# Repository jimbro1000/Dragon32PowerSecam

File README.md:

# SECAM Dragon 32 Power Board

This project is a historic record of the Dragon 32 SECAM power board.
Part Number 41504. This is not intended for fabrication but should be
dimensionally correct.

The board is unique in that it contains a full YPrPb conversion to
RGB - something very lacking from the original design

## Compatibility

This board can only be used with a SECAM version of the main CPU
board, see https://github.com/jimbro1000/Dragon32Issue2aSecam

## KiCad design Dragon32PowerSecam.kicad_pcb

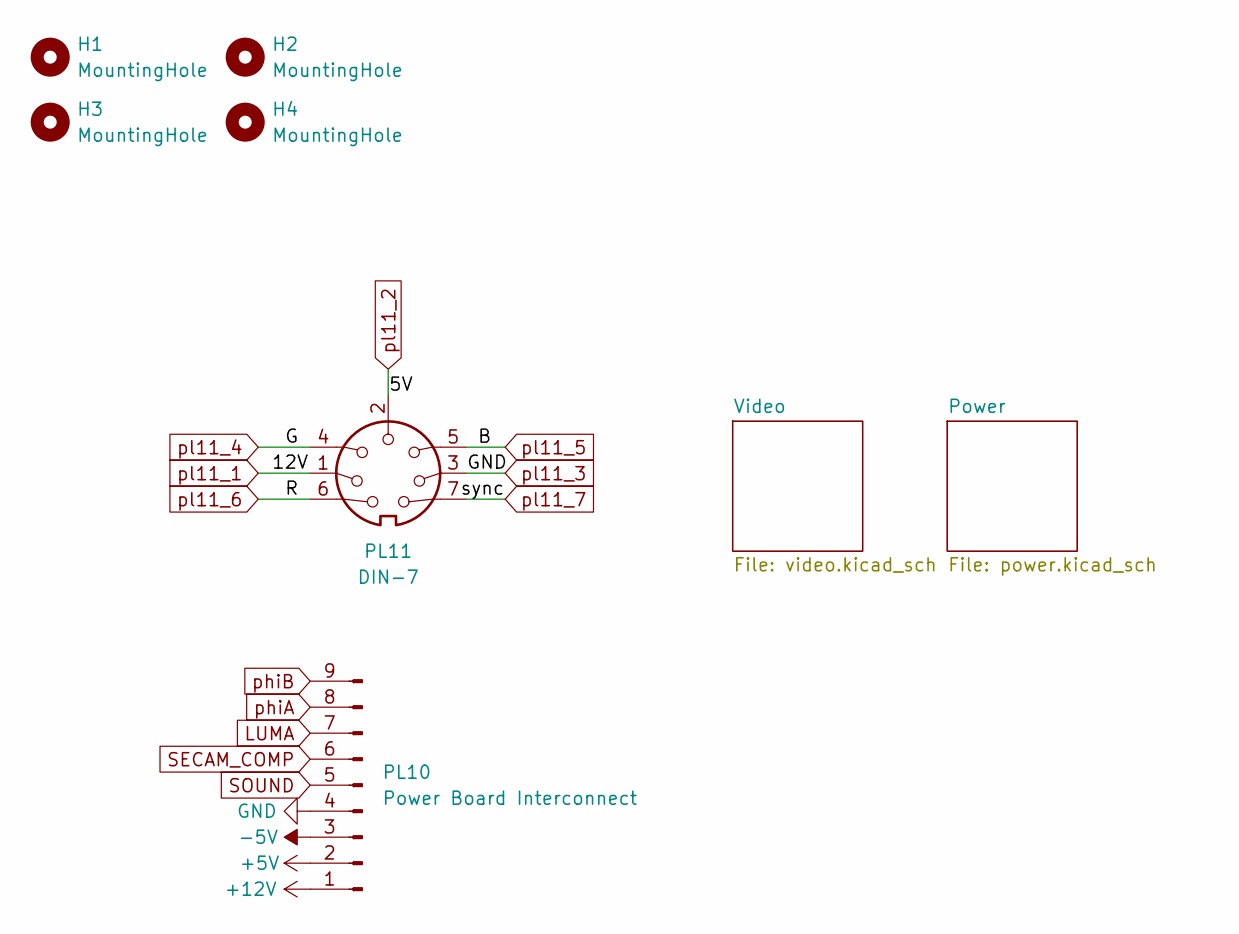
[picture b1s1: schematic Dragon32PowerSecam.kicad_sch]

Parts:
H1, H2, H3, H4: MountingHole; MountingHole_3.2mm_M3
PL10: Power Board Interconnect; Molex_KK-396_A-41791-0009_1x09_P3.96mm_Vertical; DigiKey 2057-LHD-09-TS-ND
PL11: DIN-7; CUI_SDS-70J; DigiKey CP-2370-ND

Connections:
+5V: PL10.2; also elsewhere on the board
+12V: PL10.1; also elsewhere on the board
-5V: PL10.3; also elsewhere on the board
LUMA: PL10.7; also elsewhere on the board
SECAM_COMP: PL10.6; also elsewhere on the board
SOUND: PL10.5; also elsewhere on the board
phiA: PL10.8; also elsewhere on the board
phiB: PL10.9; also elsewhere on the board
pl11_1: PL11.1; also elsewhere on the board
pl11_2: PL11.2; also elsewhere on the board
pl11_3: PL10.4, PL11.3; also elsewhere on the board
pl11_4: PL11.4; also elsewhere on the board
pl11_5: PL11.5; also elsewhere on the board
pl11_6: PL11.6; also elsewhere on the board
pl11_7: PL11.7; also elsewhere on the board

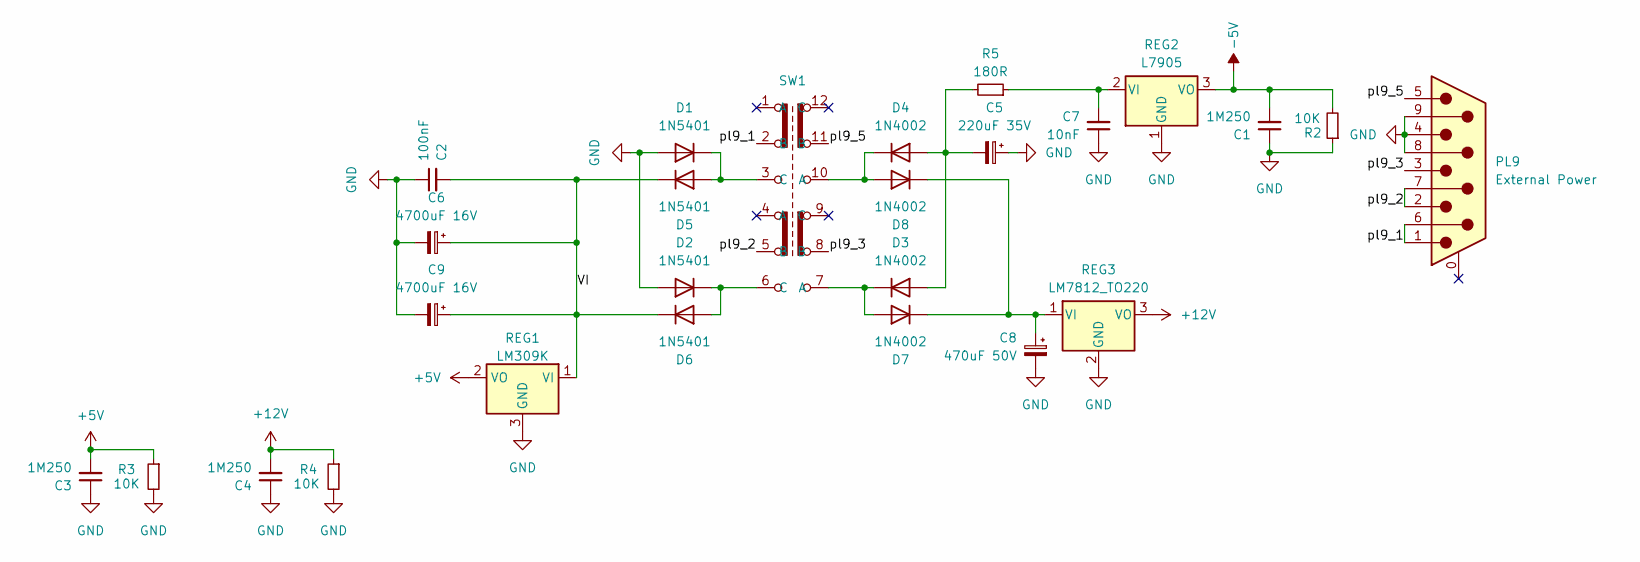
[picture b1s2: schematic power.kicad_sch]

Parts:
C1, C3, C4: 1M250; C_Rect_L16.5mm_W5.0mm_P15.00mm_MKT
C2: 100nF; C_Disc_D4.3mm_W1.9mm_P5.00mm
C5: 220uF 35V; CP_Axial_L25.0mm_D10.0mm_P30.00mm_Horizontal
C6, C9: 4700uF 16V; CP_Axial_L34.5mm_D20.0mm_P41.00mm_Horizontal
C7: 10nF; C_Disc_D4.7mm_W2.5mm_P5.00mm
C8: 470uF 50V; CP_Axial_L30.0mm_D10.0mm_P35.00mm_Horizontal
D1, D2, D5, D6: 1N5401; D_DO-201AD_P15.24mm_Horizontal
D3, D4, D7, D8: 1N4002; D_DO-41_SOD81_P10.16mm_Horizontal
PL9: External Power; DSUB-9_Male_Horizontal_P2.77x2.84mm_EdgePinOffset9.90mm_Hou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
R2, R3, R4: 10K; R_Axial_DIN0309_L9.0mm_D2.5mm_P12.70mm_Horizontal
R5: 180R; R_Axial_DIN0516_L15.5mm_D5.0mm_P20.32mm_Horizontal
REG1: LM309K; TO-3
REG2: L7905; TO-220-3_Vertical
REG3: LM7812_TO220; TO-220-3_Vertical
SW1: Switch_Push_Interlock_4P2T

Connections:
+5V: C3.2, R3.1, REG1.2 (VO); also elsewhere on the board
+12V: C4.2, R4.1, REG3.3 (VO); also elsewhere on the board
-5V: C1.2, R2.2, REG2.3 (VO); also elsewhere on the board
/Power/VI: C2.2, C6.1, C9.1, D5.1 (K), D6.1 (K), REG1.1 (VI)
/Power/pl9_1: PL9.1, PL9.6, SW1.2 (B)
/Power/pl9_2: PL9.2, PL9.7, SW1.5 (B)
/Power/pl9_3: PL9.3, SW1.8 (B)
/Power/pl9_5: PL9.5, SW1.11 (B)
unnamed: D1.1 (K), D5.2 (A), SW1.3 (C)
unnamed: D2.1 (K), D6.2 (A), SW1.6 (C)
unnamed: C5.2, D3.2 (A), D4.2 (A), R5.2
unnamed: D3.1 (K), D7.2 (A), SW1.7 (A)
unnamed: D4.1 (K), D8.2 (A), SW1.10 (A)
unnamed: C8.1, D7.1 (K), D8.1 (K), REG3.1 (VI)
unnamed: C7.2, R5.1, REG2.2 (VI)
pl11_3: C1.1, C2.1, C3.1, C4.1, C5.1, C6.2, C7.1, C8.2, C9.2, D1.2 (A), D2.2 (A), PL9.4, PL9.8, PL9.9, R2.1, R3.2, R4.2, REG1.3 (GND), REG2.1 (GND), REG3.2 (GND); also elsewhere on the board

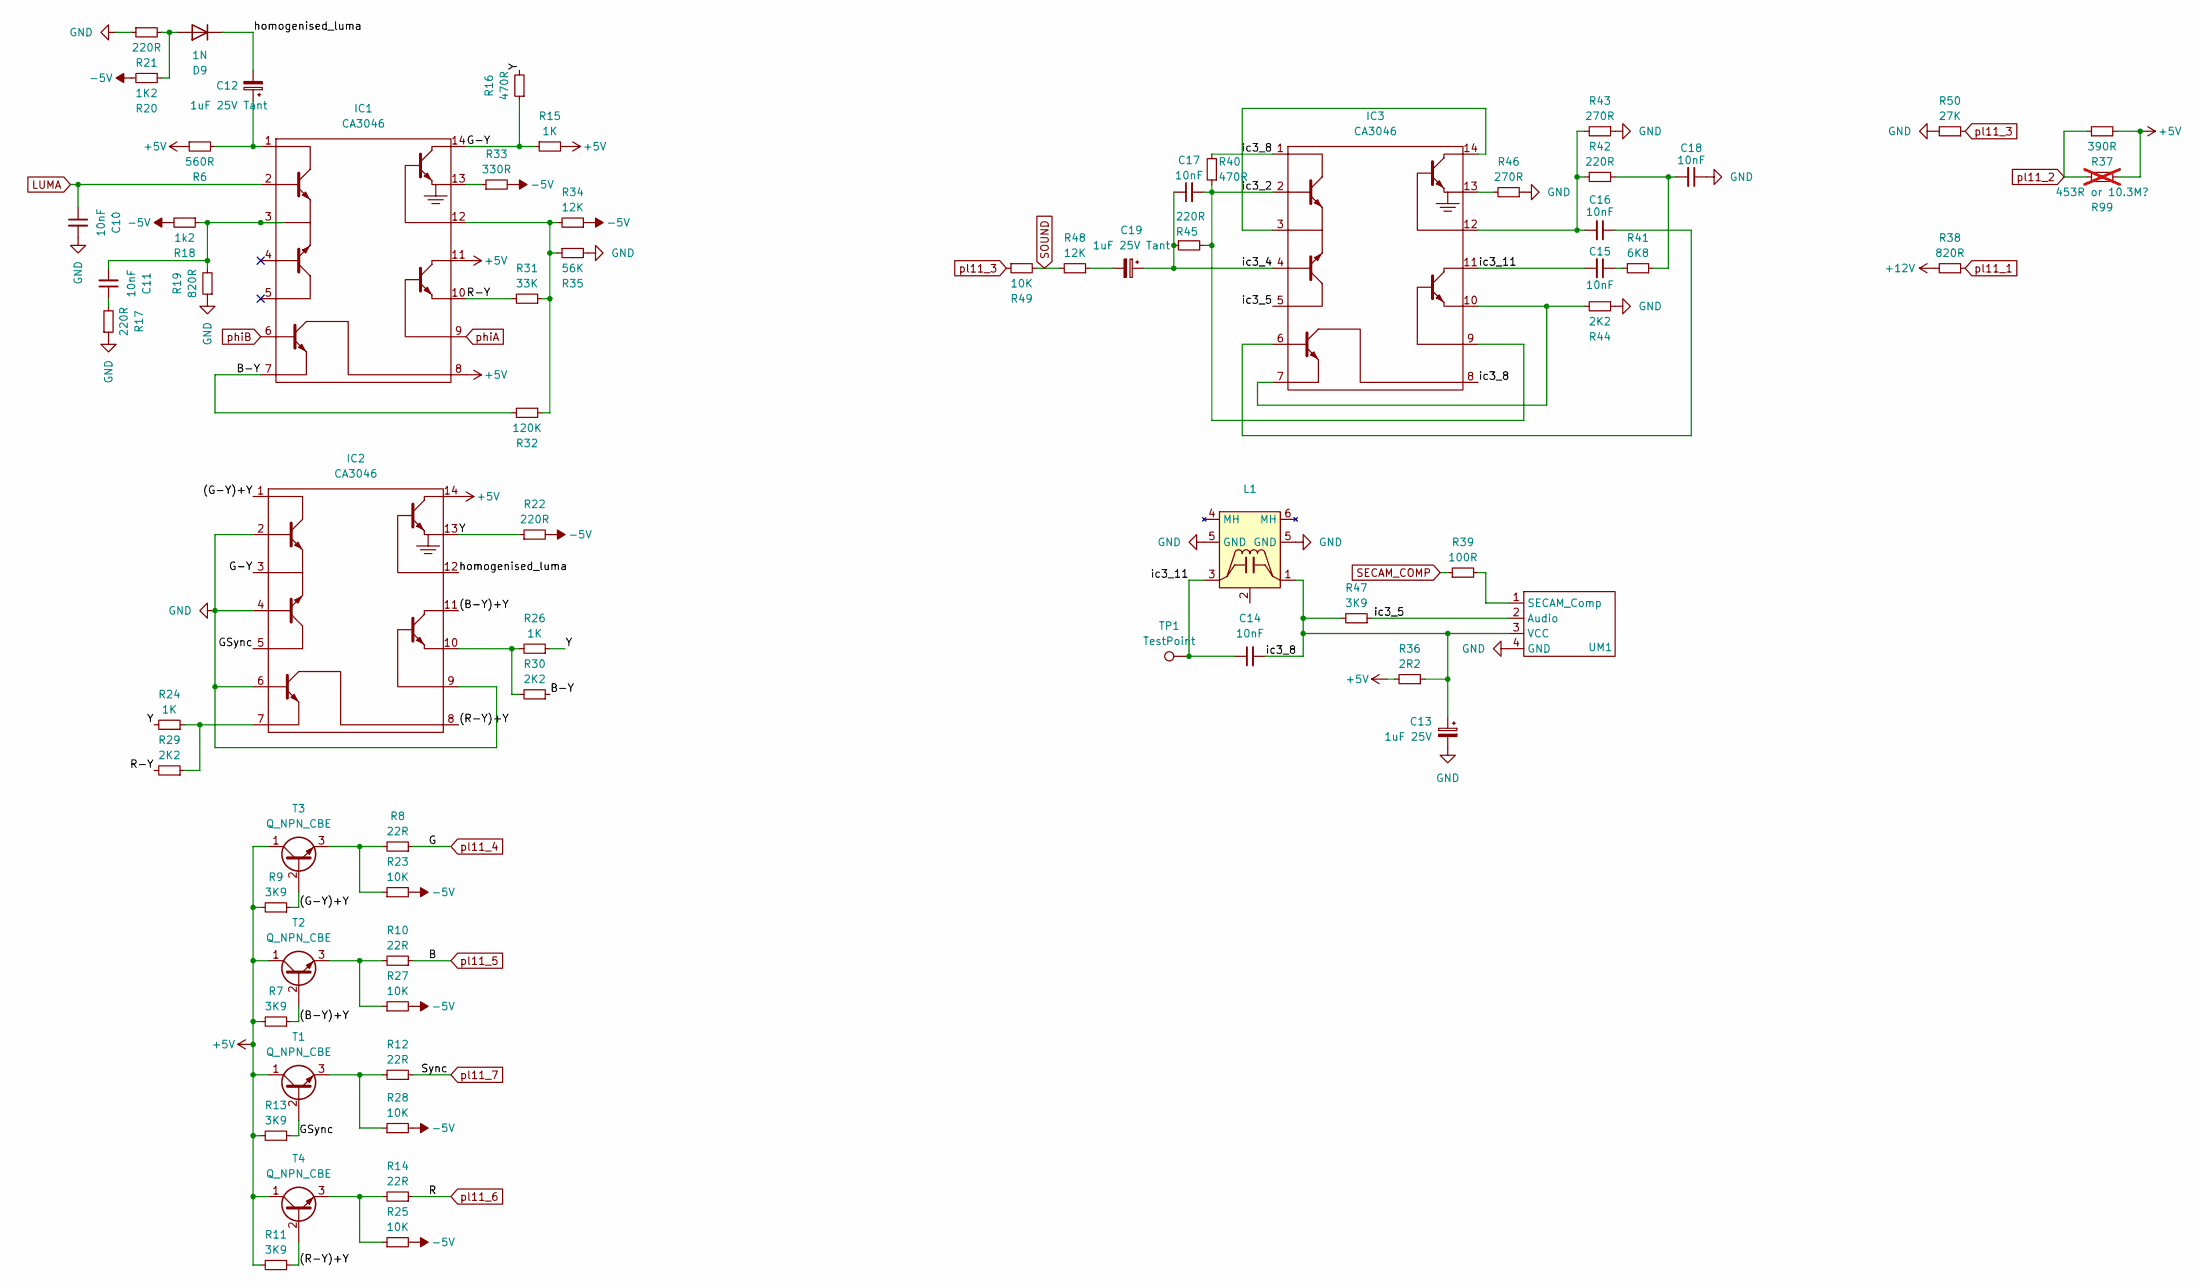
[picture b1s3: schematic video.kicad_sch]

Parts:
C10, C16: 10nF; C_Disc_D3.4mm_W2.1mm_P2.50mm
C11, C14: 10nF; C_Disc_D3.0mm_W2.0mm_P2.50mm
C12, C19: 1uF 25V Tant; CP_Radial_Tantal_D4.5mm_P5.00mm
C13: 1uF 25V; CP_Radial_Tantal_D4.5mm_P5.00mm
C15, C17, C18: 10nF; C_Disc_D4.3mm_W1.9mm_P5.00mm
D9: 1N; D_A-405_P12.70mm_Horizontal
IC1, IC2, IC3: CA3046; DIP-14_W7.62mm
L1: TOKO_RCL_10K
R6: 560R; R_Axial_DIN0309_L9.0mm_D2.5mm_P12.70mm_Horizontal
R7, R9, R11, R13, R47: 3K9; R_Axial_DIN0309_L9.0mm_D2.5mm_P12.70mm_Horizontal
R8, R10, R12, R14: 22R; R_Axial_DIN0309_L9.0mm_D2.5mm_P12.70mm_Horizontal
R15, R24, R26: 1K; R_Axial_DIN0309_L9.0mm_D2.5mm_P12.70mm_Horizontal
R16, R40: 470R; R_Axial_DIN0309_L9.0mm_D2.5mm_P12.70mm_Horizontal
R17, R21, R22, R42, R45: 220R; R_Axial_DIN0309_L9.0mm_D2.5mm_P12.70mm_Horizontal
R18: 1k2; R_Axial_DIN0207_L6.3mm_D2.5mm_P10.16mm_Horizontal
R19, R38: 820R; R_Axial_DIN0309_L9.0mm_D2.5mm_P12.70mm_Horizontal
R20: 1K2; R_Axial_DIN0207_L6.3mm_D2.5mm_P10.16mm_Horizontal
R23, R25, R27, R28, R49: 10K; R_Axial_DIN0309_L9.0mm_D2.5mm_P12.70mm_Horizontal
R29, R30, R44: 2K2; R_Axial_DIN0309_L9.0mm_D2.5mm_P12.70mm_Horizontal
R31: 33K; R_Axial_DIN0309_L9.0mm_D2.5mm_P12.70mm_Horizontal
R32: 120K; R_Axial_DIN0309_L9.0mm_D2.5mm_P12.70mm_Horizontal
R33: 330R; R_Axial_DIN0309_L9.0mm_D2.5mm_P12.70mm_Horizontal
R34, R48: 12K; R_Axial_DIN0309_L9.0mm_D2.5mm_P12.70mm_Horizontal
R35: 56K; R_Axial_DIN0309_L9.0mm_D2.5mm_P12.70mm_Horizontal
R36: 2R2; R_Axial_DIN0309_L9.0mm_D2.5mm_P12.70mm_Horizontal
R37: 390R; R_Axial_DIN0309_L9.0mm_D2.5mm_P12.70mm_Horizontal
R39: 100R; R_Axial_DIN0309_L9.0mm_D2.5mm_P12.70mm_Horizontal
R41: 6K8; R_Axial_DIN0309_L9.0mm_D2.5mm_P12.70mm_Horizontal
R43, R46: 270R; R_Axial_DIN0309_L9.0mm_D2.5mm_P12.70mm_Horizontal
R50: 27K; R_Axial_DIN0309_L9.0mm_D2.5mm_P12.70mm_Horizontal
R99: 453R or 10.3M?; R_Axial_DIN0309_L9.0mm_D2.5mm_P12.70mm_Horizontal; not fitted
T1, T2, T3, T4: Q_NPN_CBE; TO-92_Wide
TP1: TestPoint; TestPoint_THTPad_D1.0mm_Drill0.5mm
UM1: RF_Modulator_Astec_UM1601

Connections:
+5V: IC1.8, IC1.11, IC2.14, R6.1, R7.2, R9.2, R11.2, R13.2, R15.2, R36.2, R37.2, R99.2, T1.1 (C), T2.1 (C), T3.1 (C), T4.1 (C); also elsewhere on the board
+12V: R38.2; also elsewhere on the board
-5V: R18.2, R20.2, R22.2, R23.2, R25.2, R27.2, R28.2, R33.2, R34.1; also elsewhere on the board
/Video/(B-Y)+Y: IC2.11, R7.1, T2.2 (B)
/Video/(G-Y)+Y: IC2.1, R9.1, T3.2 (B)
/Video/(R-Y)+Y: IC2.8, R11.1, T4.2 (B)
/Video/B-Y: IC1.7, R30.1, R32.2
/Video/G-Y: IC1.14, IC2.3, R15.1, R16.1
/Video/GSync: IC2.5, R13.1, T1.2 (B)
/Video/R-Y: IC1.10, R29.2, R31.2
/Video/Y: IC2.13, R16.2, R22.1, R24.2, R26.1
/Video/homogenised_luma: C12.2, D9.1 (K), IC2.12
/Video/ic3_2: C17.2, IC3.2, IC3.9, R40.1, R45.2
/Video/ic3_4: C17.1, C19.1, IC3.4, R45.1
/Video/ic3_5: IC3.5, R47.1, UM1.2 (Audio)
/Video/ic3_8: C13.1, C14.2, IC3.1, IC3.8, L1.1, R36.1, R40.2, R47.2, UM1.3 (VCC)
/Video/ic3_11: C14.1, C15.2, IC3.11, L1.3, TP1.1
LUMA: C10.1, IC1.2; also elsewhere on the board
unnamed: C11.1, R17.2
unnamed: C11.2, IC1.3, R18.1, R19.2
unnamed: C12.1, IC1.1, R6.2
unnamed: C15.1, R41.2
unnamed: C16.1, IC3.6
unnamed: C16.2, IC3.12, R42.2, R43.2
unnamed: C18.2, R41.1, R42.1
unnamed: C19.2, R48.1
unnamed: D9.2 (A), R20.1, R21.2
unnamed: IC1.12, R31.1, R32.1, R34.2, R35.1
unnamed: IC1.13, R33.1
unnamed: IC2.7, R24.1, R29.1
unnamed: IC2.10, R26.2, R30.2
unnamed: IC3.7, IC3.10, R44.2
unnamed: IC3.13, R46.2
unnamed: IC3.3, IC3.14
unnamed: R12.2, R28.1, T1.3 (E)
unnamed: R10.2, R27.1, T2.3 (E)
unnamed: R8.2, R23.1, T3.3 (E)
unnamed: R14.2, R25.1, T4.3 (E)
unnamed: R39.2, UM1.1 (SECAM_Comp)
SECAM_COMP: R39.1; also elsewhere on the board
SOUND: R48.2, R49.2; also elsewhere on the board
phiA: IC1.9; also elsewhere on the board
phiB: IC1.6; also elsewhere on the board
pl11_1: R38.1; also elsewhere on the board
pl11_2: R37.1, R99.1; also elsewhere on the board
pl11_3: C10.2, C13.2, C18.1, IC2.2, IC2.4, IC2.6, IC2.9, L1.5 (GND), R17.1, R19.1, R21.1, R35.2, R43.1, R44.1, R46.1, R49.1, R50.1, R50.2, UM1.4 (GND); also elsewhere on the board
pl11_4: R8.1; also elsewhere on the board
pl11_5: R10.1; also elsewhere on the board
pl11_6: R14.1; also elsewhere on the board
pl11_7: R12.1; also elsewhere on the board

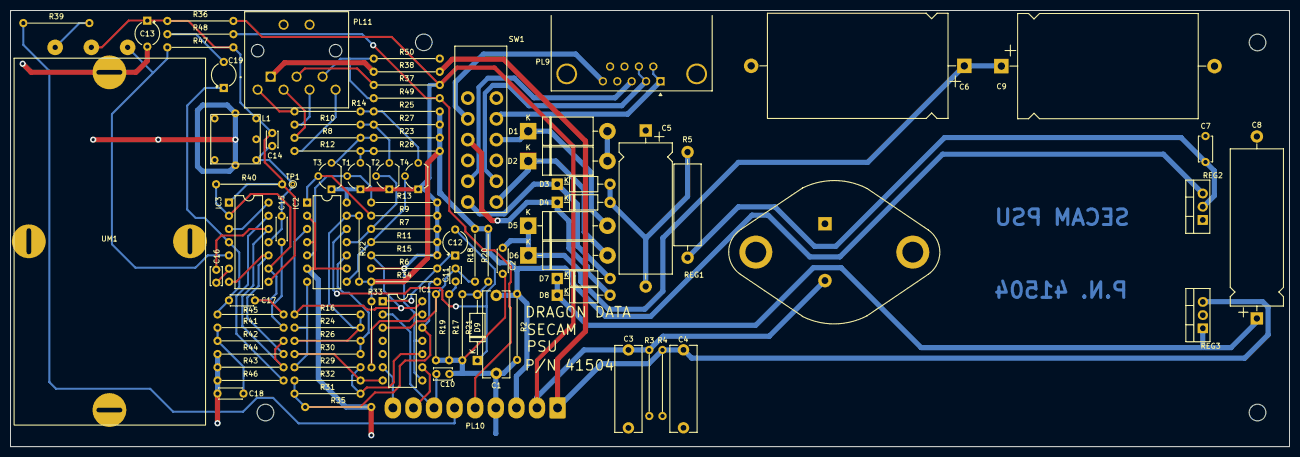
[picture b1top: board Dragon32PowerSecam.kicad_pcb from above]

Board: 2 copper layers, 246.0 x 83.9 mm, 98 parts (0 on the bottom side), 62 nets.

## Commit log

2025-02-04 initial layout
2025-02-04 video tracing
2025-02-07 more video tracing
2025-02-07 power tracing
2025-02-09 layout and routing complete
2025-02-09 rationalise video
2025-02-10 rationalise rgb circuit
2025-02-17 update labelling
2025-02-18 label rf can
